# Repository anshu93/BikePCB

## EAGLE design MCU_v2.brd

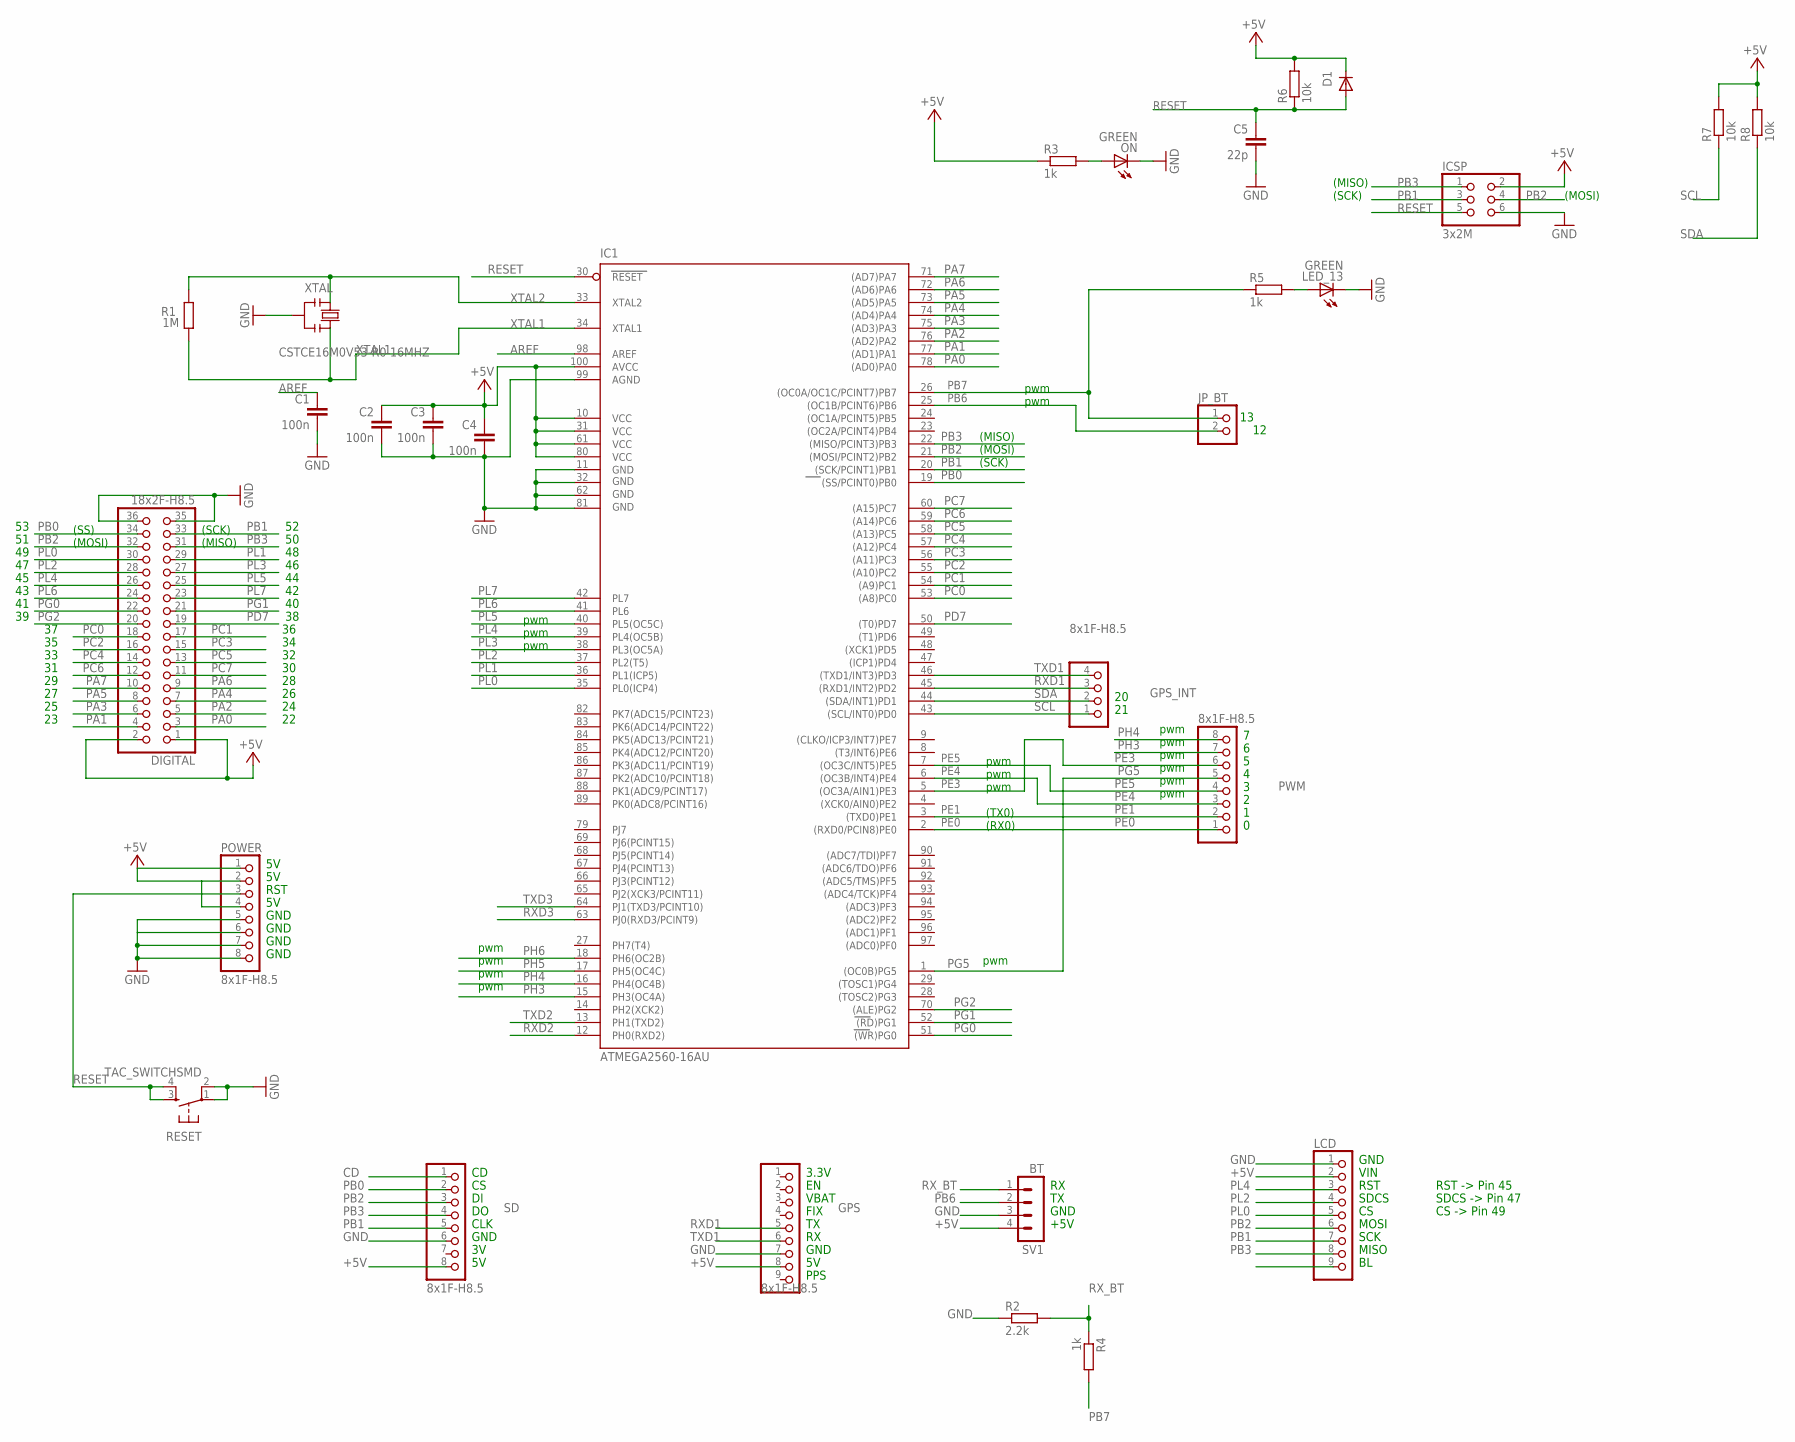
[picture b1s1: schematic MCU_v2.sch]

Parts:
C1, C2, C3, C4: 100n; C0805
C5: 22p; C0805
D1: DIODE-MINIMELF; MINIMELF
DIGITAL: 18x2F-H8.5; 2X18
GPS: 8x1F-H8.5; 1X09
GPS_INT: 8x1F-H8.5; 1X04
IC1: ATMEGA2560-16AU; TQFP100
ICSP: 3x2M; 2X03
JP_BT: PINHD-1X2; 1X02
LCD: PINHD-1X9; 1X09
LED_13: GREEN; CHIP-LED0805
ON: GREEN; CHIP-LED0805
POWER: 8x1F-H8.5; 1X08
PWM: 8x1F-H8.5; 1X08
R1: 1M; R0805
R2: 2.2k; R0805
R3, R4, R5: 1k; R0805
R6, R7, R8: 10k; R0805
RESET: TAC_SWITCHSMD; TACTILE-SWITCH-SMD
SD: 8x1F-H8.5; 1X08
SV1: BT; MA04-1
XTAL: CSTCE16M0V53-R0 16MHZ; RESONATOR

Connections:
+5V: C2.1, C3.1, C4.1, D1.C, DIGITAL.1, DIGITAL.2, GPS.8, IC1.10 (VCC), IC1.31 (VCC1), IC1.61 (VCC2), IC1.80 (VCC3), IC1.100 (AVCC), ICSP.2, LCD.2, POWER.1, POWER.2, POWER.4, R3.1, R6.2, R7.2, R8.2, SD.8, SV1.4
AREF: C1.1, IC1.98 (AREF)
CD: SD.1
GND: C1.2, C2.2, C3.2, C4.2, C5.2, DIGITAL.35, DIGITAL.36, GPS.7, IC1.11 (GND), IC1.32 (GND1), IC1.62 (GND2), IC1.81 (GND3), IC1.99 (AGND), ICSP.6, LCD.1, LED_13.C, ON.C, POWER.5, POWER.6, POWER.7, POWER.8, R2.1, RESET.1, RESET.2, SD.6, SV1.3, XTAL.2
unnamed: LED_13.A, R5.2
unnamed: ON.A, R3.2
PA0: DIGITAL.3, IC1.78 ((AD0)PA0)
PA1: DIGITAL.4, IC1.77 ((AD1)PA1)
PA2: DIGITAL.5, IC1.76 ((AD2)PA2)
PA3: DIGITAL.6, IC1.75 ((AD3)PA3)
PA4: DIGITAL.7, IC1.74 ((AD4)PA4)
PA5: DIGITAL.8, IC1.73 ((AD5)PA5)
PA6: DIGITAL.9, IC1.72 ((AD6)PA6)
PA7: DIGITAL.10, IC1.71 ((AD7)PA7)
PB0: DIGITAL.34, IC1.19 ((SS/PCINT0)PB0), SD.2
PB1: DIGITAL.33, IC1.20 ((SCK/PCINT1)PB1), ICSP.3, LCD.7, SD.5
PB2: DIGITAL.32, IC1.21 ((MOSI/PCINT2)PB2), ICSP.4, LCD.6, SD.3
PB3: DIGITAL.31, IC1.22 ((MISO/PCINT3)PB3), ICSP.1, LCD.8, SD.4
PB6: IC1.25 ((OC1B/PCINT6)PB6), JP_BT.2, SV1.2
PB7: IC1.26 ((OC0A/OC1C/PCINT7)PB7), JP_BT.1, R4.2, R5.1
PC0: DIGITAL.18, IC1.53 ((A8)PC0)
PC1: DIGITAL.17, IC1.54 ((A9)PC1)
PC2: DIGITAL.16, IC1.55 ((A10)PC2)
PC3: DIGITAL.15, IC1.56 ((A11)PC3)
PC4: DIGITAL.14, IC1.57 ((A12)PC4)
PC5: DIGITAL.13, IC1.58 ((A13)PC5)
PC6: DIGITAL.12, IC1.59 ((A14)PC6)
PC7: DIGITAL.11, IC1.60 ((A15)PC7)
PD7: DIGITAL.19, IC1.50 ((T0)PD7)
PE0: IC1.2 ((RXD0/PCIN8)PE0), PWM.1
PE1: IC1.3 ((TXD0)PE1), PWM.2
PE3: IC1.5 ((OC3A/AIN1)PE3), PWM.6
PE4: IC1.6 ((OC3B/INT4)PE4), PWM.3
PE5: IC1.7 ((OC3C/INT5)PE5), PWM.4
PG0: DIGITAL.22, IC1.51 ((WR)PG0)
PG1: DIGITAL.21, IC1.52 ((RD)PG1)
PG2: DIGITAL.20, IC1.70 ((ALE)PG2)
PG5: IC1.1 ((OC0B)PG5), PWM.5
PH3: IC1.15 (PH3(OC4A)), PWM.7
PH4: IC1.16 (PH4(OC4B)), PWM.8
PH5: IC1.17 (PH5(OC4C))
PH6: IC1.18 (PH6(OC2B))
PL0: DIGITAL.30, IC1.35 (PL0(ICP4)), LCD.5
PL1: DIGITAL.29, IC1.36 (PL1(ICP5))
PL2: DIGITAL.28, IC1.37 (PL2(T5)), LCD.4
PL3: DIGITAL.27, IC1.38 (PL3(OC5A))
PL4: DIGITAL.26, IC1.39 (PL4(OC5B)), LCD.3
PL5: DIGITAL.25, IC1.40 (PL5(OC5C))
PL6: DIGITAL.24, IC1.41 (PL6)
PL7: DIGITAL.23, IC1.42 (PL7)
RESET: C5.1, D1.A, IC1.30 (RESET), ICSP.5, POWER.3, R6.1, RESET.3, RESET.4
RXD1: GPS.5, GPS_INT.3, IC1.45 ((RXD1/INT2)PD2)
RXD2: IC1.12 (PH0(RXD2))
RXD3: IC1.63 (PJ0(RXD3/PCINT9))
RX_BT: R2.2, R4.1, SV1.1
SCL: GPS_INT.1, IC1.43 ((SCL/INT0)PD0), R7.1
SDA: GPS_INT.2, IC1.44 ((SDA/INT1)PD1), R8.1
TXD1: GPS.6, GPS_INT.4, IC1.46 ((TXD1/INT3)PD3)
TXD2: IC1.13 (PH1(TXD2))
TXD3: IC1.64 (PJ1(TXD3/PCINT10))
XTAL1: IC1.34 (XTAL1), R1.1, XTAL.3
XTAL2: IC1.33 (XTAL2), R1.2, XTAL.1

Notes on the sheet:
(SCK)
(MISO)
(MOSI)
pwm
(TX0)
(RX0)
(SS)
CLK
GND
FIX
VBAT
3.3V
+5V
VIN
RST
SDCS
MOSI
SCK
MISO
CS -> Pin 49
SDCS -> Pin 47
RST -> Pin 45
PPS

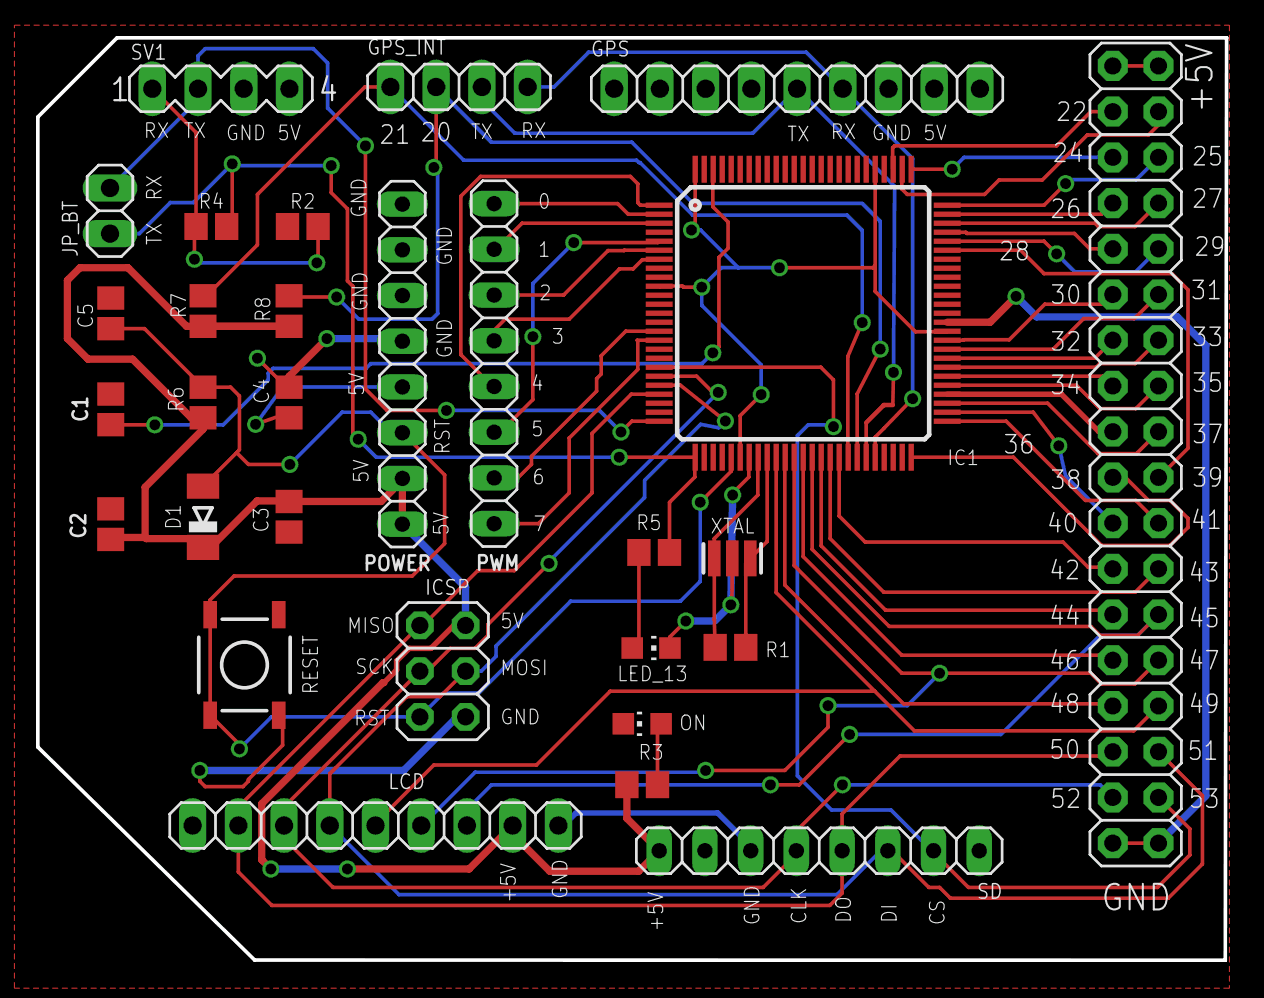
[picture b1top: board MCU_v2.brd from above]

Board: 2 copper layers, 66.0 x 51.2 mm, 29 parts (0 on the bottom side), 55 nets.

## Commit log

2015-02-23 Initial schematic ready
2015-02-23 Corrected GPS module
2015-02-23 Set up power nodes
2015-02-23 Put in correct component footprints
2015-02-24 Board ready but still has some DRC errors
2015-02-24 Made the power traces thicker

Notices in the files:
parts and their libraries:
SparkFun-Retired: Licensing:Creative Commons ShareAlike 4.0 International - https://creativecommons.org/licenses/by-sa/4.0
